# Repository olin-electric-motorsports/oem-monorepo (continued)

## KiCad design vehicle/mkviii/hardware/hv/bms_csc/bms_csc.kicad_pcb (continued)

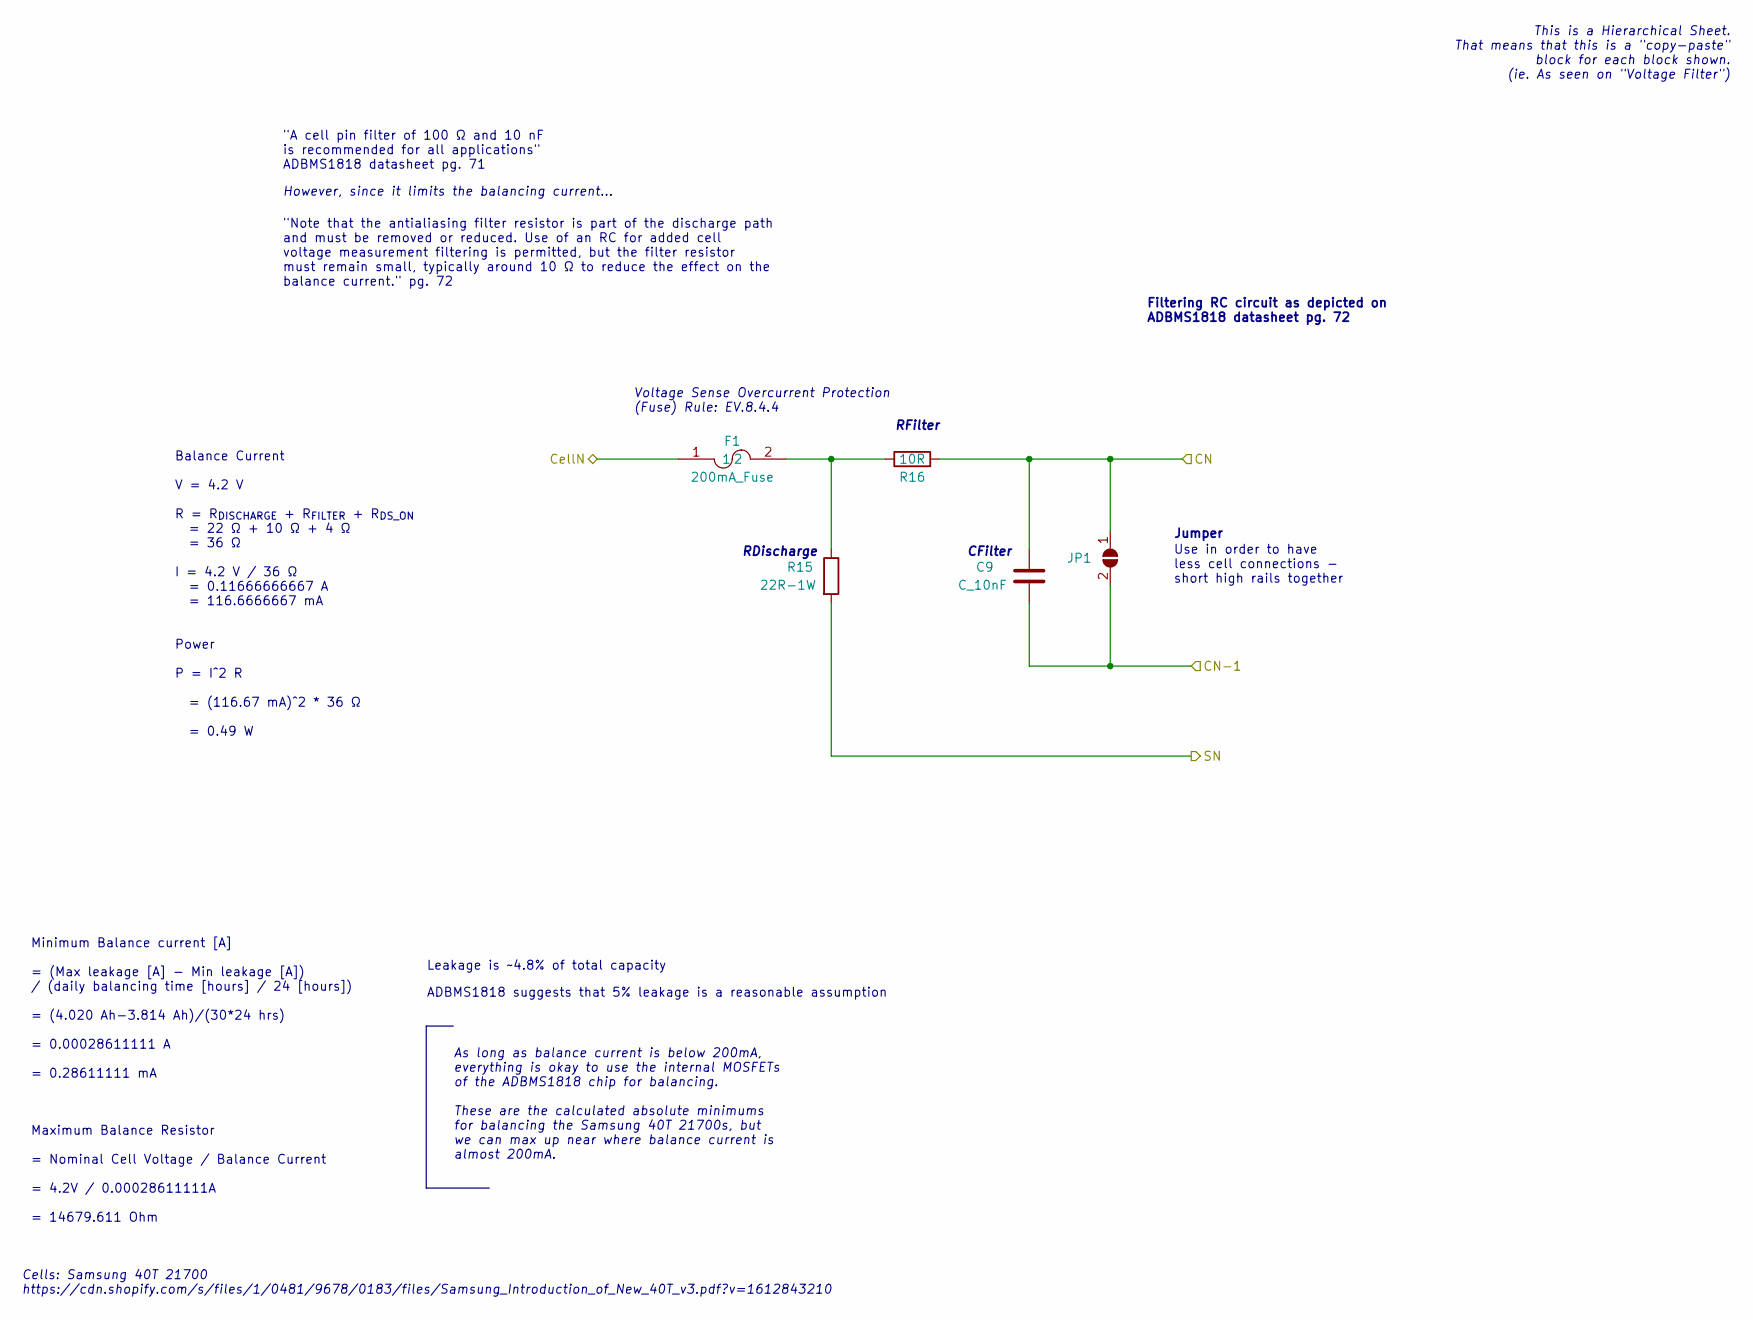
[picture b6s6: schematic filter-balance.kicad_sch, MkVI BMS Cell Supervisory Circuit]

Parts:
C9: C_10nF; C_0603; MPN CL10B103KB8NNNC
F1: 200mA_Fuse; Fuse_1206_3216Metric; MPN 0466.200NRHF
JP1: SolderJumper_2_Open; SolderJumper-2_P1.3mm_Open_TrianglePad1.0x1.5mm
R15: 22R-1W; R_2512_6332Metric; MPN 352022RJT
R16: 10R; R_0603; MPN SG73P1JTTD100J

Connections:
/C15: C9.2, JP1.2 (B); also elsewhere on the board
/C16: C9.1, JP1.1 (A), R16.2; also elsewhere on the board
/CELL16: F1.1; also elsewhere on the board
/S16: R15.2; also elsewhere on the board
unnamed: F1.2, R15.1, R16.1

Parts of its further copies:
C10, C11, C12, C13, C14, C15, C16, C17, C18, C19, C20, C21, C22, C23, C24, C25, C26: C_10nF; C_0603; MPN CL10B103KB8NNNC
F2, F3, F4, F5, F6, F7, F8, F9, F10, F11, F12, F13, F14, F15, F16, F17, F18: 200mA_Fuse; Fuse_1206_3216Metric; MPN 0466.200NRHF
JP2, JP3, JP4, JP5, JP6, JP7, JP8, JP9, JP10, JP11, JP12, JP13, JP14, JP15, JP16, JP17, JP18: SolderJumper_2_Open; SolderJumper-2_P1.3mm_Open_TrianglePad1.0x1.5mm
R17, R19, R21, R23, R25, R27, R29, R31, R33, R35, R37, R39, R41, R43, R45, R47, R49: 22R-1W; R_2512_6332Metric; MPN 352022RJT
R18, R20, R22, R24, R26, R28, R30, R32, R34, R36, R38, R40, R42, R44, R46, R48, R50: 10R; R_0603; MPN SG73P1JTTD100J

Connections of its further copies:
/C1: C25.2, C26.1, JP17.2 (B), JP18.1 (A), R50.2; also elsewhere on the board
/C2: C24.2, C25.1, JP16.2 (B), JP17.1 (A), R48.2; also elsewhere on the board
/C3: C23.2, C24.1, JP15.2 (B), JP16.1 (A), R46.2; also elsewhere on the board
/C4: C22.2, C23.1, JP14.2 (B), JP15.1 (A), R44.2; also elsewhere on the board
/C5: C21.2, C22.1, JP13.2 (B), JP14.1 (A), R42.2; also elsewhere on the board
/C6: C20.2, C21.1, JP12.2 (B), JP13.1 (A), R40.2; also elsewhere on the board
/C7: C19.2, C20.1, JP11.2 (B), JP12.1 (A), R38.2; also elsewhere on the board
/C8: C18.2, C19.1, JP10.2 (B), JP11.1 (A), R36.2; also elsewhere on the board
/C9: C17.2, C18.1, JP9.2 (B), JP10.1 (A), R34.2; also elsewhere on the board
/C10: C16.2, C17.1, JP8.2 (B), JP9.1 (A), R32.2; also elsewhere on the board
/C11: C15.2, C16.1, JP7.2 (B), JP8.1 (A), R30.2; also elsewhere on the board
/C12: C14.2, C15.1, JP6.2 (B), JP7.1 (A), R28.2; also elsewhere on the board
/C13: C13.2, C14.1, JP5.2 (B), JP6.1 (A), R26.2; also elsewhere on the board
/C14: C12.2, C13.1, JP4.2 (B), JP5.1 (A), R24.2; also elsewhere on the board
/C15: C12.1, JP4.1 (A), R22.2; also elsewhere on the board
/C16: C11.2, JP3.2 (B); also elsewhere on the board
/C17: C10.2, C11.1, JP2.2 (B), JP3.1 (A), R20.2; also elsewhere on the board
/C18: C10.1, JP2.1 (A), R18.2; also elsewhere on the board
/CELL1: F18.1; also elsewhere on the board
/CELL2: F17.1; also elsewhere on the board
/CELL3: F16.1; also elsewhere on the board
/CELL4: F15.1; also elsewhere on the board
/CELL5: F14.1; also elsewhere on the board
/CELL6: F13.1; also elsewhere on the board
/CELL7: F12.1; also elsewhere on the board
/CELL8: F11.1; also elsewhere on the board
/CELL9: F10.1; also elsewhere on the board
/CELL10: F9.1; also elsewhere on the board
/CELL11: F8.1; also elsewhere on the board
/CELL12: F7.1; also elsewhere on the board
/CELL13: F6.1; also elsewhere on the board
/CELL14: F5.1; also elsewhere on the board
/CELL15: F4.1; also elsewhere on the board
/CELL17: F3.1; also elsewhere on the board
/CELL18: F2.1; also elsewhere on the board
/S1: R49.2; also elsewhere on the board
/S2: R47.2; also elsewhere on the board
/S3: R45.2; also elsewhere on the board
/S4: R43.2; also elsewhere on the board
/S5: R41.2; also elsewhere on the board
/S6: R39.2; also elsewhere on the board
/S7: R37.2; also elsewhere on the board
/S8: R35.2; also elsewhere on the board
/S9: R33.2; also elsewhere on the board
/S10: R31.2; also elsewhere on the board
/S11: R29.2; also elsewhere on the board
/S12: R27.2; also elsewhere on the board
/S13: R25.2; also elsewhere on the board
/S14: R23.2; also elsewhere on the board
/S15: R21.2; also elsewhere on the board
/S17: R19.2; also elsewhere on the board
/S18: R17.2; also elsewhere on the board
unnamed: F2.2, R17.1, R18.1
unnamed: F3.2, R19.1, R20.1
unnamed: F4.2, R21.1, R22.1
unnamed: F5.2, R23.1, R24.1
unnamed: F6.2, R25.1, R26.1
unnamed: F7.2, R27.1, R28.1
unnamed: F8.2, R29.1, R30.1
unnamed: F9.2, R31.1, R32.1
unnamed: F10.2, R33.1, R34.1
unnamed: F11.2, R35.1, R36.1
unnamed: F12.2, R37.1, R38.1
unnamed: F13.2, R39.1, R40.1
unnamed: F14.2, R41.1, R42.1
unnamed: F15.2, R43.1, R44.1
unnamed: F16.2, R45.1, R46.1
unnamed: F17.2, R47.1, R48.1
unnamed: F18.2, R49.1, R50.1

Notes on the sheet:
RDischarge
Leakage is ~4.8% of total capacity
Use in order to have less cell connections - short high rails together
"A cell pin filter of 100 Ω and 10 nF is recommended for all applications" ADBMS1818 datasheet pg. 71
This is a Hierarchical Sheet. That means that this is a "copy-paste" block for each block shown. (ie. As seen on "Voltage Filter")
CFilter
"Note that the antialiasing filter resistor is part of the discharge path and must be removed or reduced. Use of an RC for added cell voltage measurement filtering is permitted, but the filter resistor must remain small, typically around 10 Ω to reduce the effect on the balance current." pg. 72
Maximum Balance Resistor = Nominal Cell Voltage / Balance Current = 4.2V / 0.00028611111A = 14679.611 Ohm
However, since it limits the balancing current...
Minimum Balance current [A] = (Max leakage [A] - Min leakage [A]) / (daily balancing time [hours] / 24 [hours]) = (4.020 Ah-3.814 Ah)/(30*24 hrs) = 0.00028611111 A = 0.28611111 mA
ADBMS1818 suggests that 5% leakage is a reasonable assumption
Jumper
Voltage Sense Overcurrent Protection (Fuse) Rule: EV.8.4.4
As long as balance current is below 200mA, everything is okay to use the internal MOSFETs of the ADBMS1818 chip for balancing. These are the calculated absolute minimums for balancing the Samsung 40T 21700s, but we can max up near where balance current is almost 200mA.
Filtering RC circuit as depicted on ADBMS1818 datasheet pg. 72
RFilter
Balance Current V = 4.2 V R = R_{DISCHARGE} + R_{FILTER} + R_{DS_ON} = 22 Ω + 10 Ω + 4 Ω = 36 Ω I = 4.2 V / 36 Ω = 0.11666666667 A = 116.6666667 mA Power P = I^2 R = (116.67 mA)^2 * 36 Ω = 0.49 W
Cells: Samsung 40T 21700 https://cdn.shopify.com/s/files/1/0481/9678/0183/files/Samsung_Introduction_of_New_40T_v3.pdf?v=1612843210

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
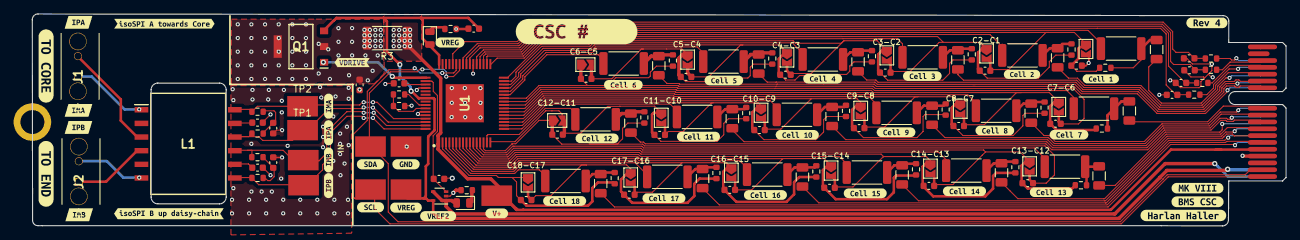
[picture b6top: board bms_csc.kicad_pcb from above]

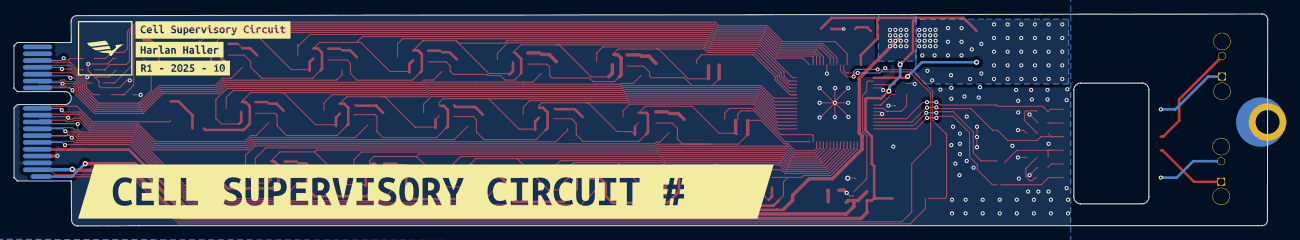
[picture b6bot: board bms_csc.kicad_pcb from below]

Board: 2 copper layers, 183.7 x 31.1 mm, 181 parts (4 on the bottom side), 106 nets.

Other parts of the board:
kibuzzard-63B4D82F: G***; kibuzzard-63B4D82F
kibuzzard-63B4D834: G***; kibuzzard-63B4D834
kibuzzard-63B4E58E: G***; kibuzzard-63B4E58E
kibuzzard-63B4E59A: G***; kibuzzard-63B4E59A
kibuzzard-63B4E581: G***; kibuzzard-63B4E581
kibuzzard-63B4E593: G***; kibuzzard-63B4E593
kibuzzard-63B4EB9B: G***; kibuzzard-63B4EB9B
kibuzzard-63B4EBA9: G***; kibuzzard-63B4EBA9
kibuzzard-63B4EBAD: G***; kibuzzard-63B4EBAD
kibuzzard-63B4EBB3: G***; kibuzzard-63B4EBB3
kibuzzard-63B4EBB8: G***; kibuzzard-63B4EBB8
kibuzzard-63B4EBF9: G***; kibuzzard-63B4EBF9
kibuzzard-63B4EC1B: G***; kibuzzard-63B4EC1B
kibuzzard-63B4EC4E: G***; kibuzzard-63B4EC4E
kibuzzard-63B4EC5B: G***; kibuzzard-63B4EC5B
kibuzzard-63B4EC6B: G***; kibuzzard-63B4EC6B
kibuzzard-63B4EC7A: G***; kibuzzard-63B4EC7A
kibuzzard-63B4EC20: G***; kibuzzard-63B4EC20
kibuzzard-63B4EC53: G***; kibuzzard-63B4EC53
kibuzzard-63B4EC66: G***; kibuzzard-63B4EC66
kibuzzard-63B4EC74: G***; kibuzzard-63B4EC74
kibuzzard-63B4EC80: G***; kibuzzard-63B4EC80
kibuzzard-63B4ED2A: G***; kibuzzard-63B4ED2A
kibuzzard-63B4ED25: G***; kibuzzard-63B4ED25
kibuzzard-63B4ED94: G***; kibuzzard-63B4ED94
kibuzzard-673A717E: G***; kibuzzard-673A717E
kibuzzard-673A718C: G***; kibuzzard-673A718C
kibuzzard-673A725C: G***; kibuzzard-673A725C
kibuzzard-673A7176: G***; kibuzzard-673A7176
kibuzzard-673A7184: G***; kibuzzard-673A7184
kibuzzard-673AA1F5: G***; kibuzzard-673AA1F5
kibuzzard-673AA1FB: G***; kibuzzard-673AA1FB
kibuzzard-673AA20C: G***; kibuzzard-673AA20C
kibuzzard-673AA233: G***; kibuzzard-673AA233
kibuzzard-691FAACE: G***; kibuzzard-691FAACE
kibuzzard-6736A7FC: G***; kibuzzard-6736A7FC
kibuzzard-6736A805: G***; kibuzzard-6736A805
kibuzzard-6736A828: G***; kibuzzard-6736A828
kibuzzard-6736A857: G***; kibuzzard-6736A857
kibuzzard-6736A863: G***; kibuzzard-6736A863
kibuzzard-6902CBBF: G***; kibuzzard-6902CBBF
kibuzzard-6902E3D6: G***; kibuzzard-6902E3D6
kibuzzard-673993C6: G***; kibuzzard-673993C6
kibuzzard-673998AC: G***; kibuzzard-673998AC
kibuzzard-69001352: G***; kibuzzard-69001352
kibuzzard-69001366: G***; kibuzzard-69001366
kibuzzard-69001374: G***; kibuzzard-69001374

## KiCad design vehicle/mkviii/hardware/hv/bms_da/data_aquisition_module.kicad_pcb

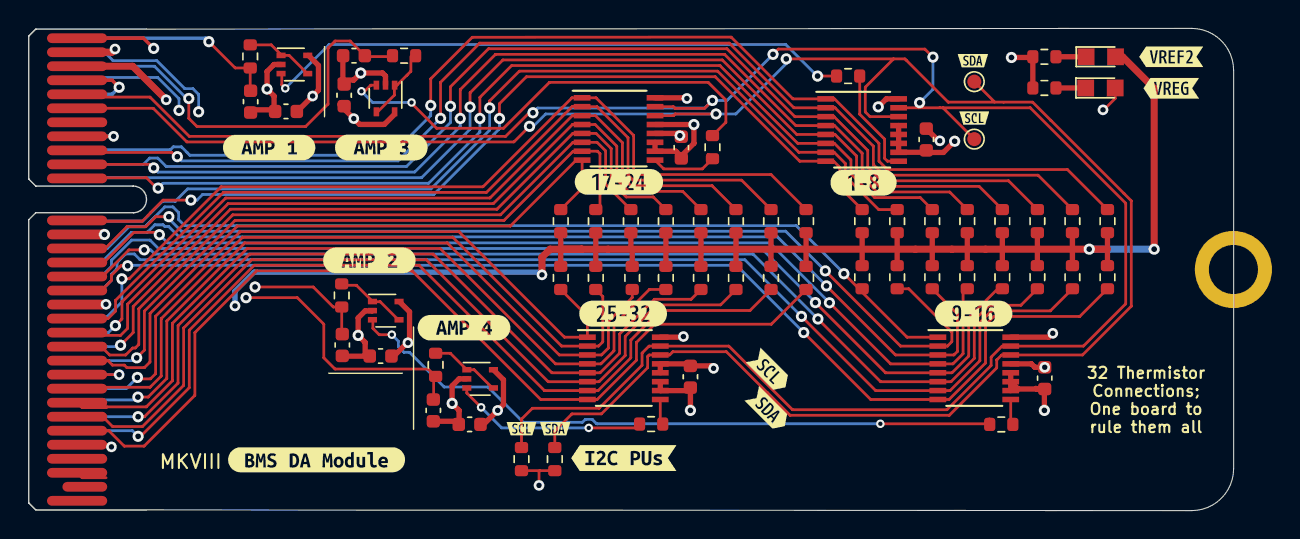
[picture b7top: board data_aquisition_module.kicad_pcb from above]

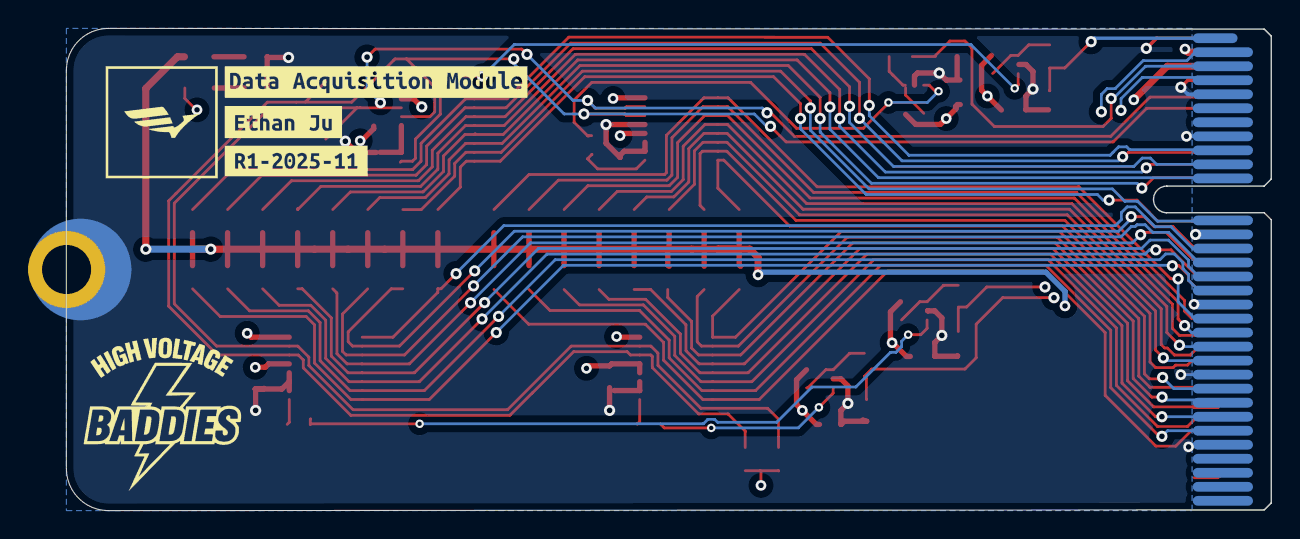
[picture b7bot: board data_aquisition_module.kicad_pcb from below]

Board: 4 copper layers, 86.0 x 34.4 mm, 91 parts (3 on the bottom side), 55 nets.

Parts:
C1, C2, C3, C4: C_1uF; C_0603
C5, C6, C7, C8, C9, C10, C11, C12: 1uF; C_0603
H2: CONN_MountingHole; PCIe_Mount
J1: CONN_pcie_x4; pcie_x4
PD1, PD2: WHITE; CHIPLED_0805
R1, R2, R3, R4, R5, R6, R7, R8, R9, R10, R11, R12, R13, R14, R15, R16, R17, R18, R19, R20, R21, R22, R23, R24, R25, R26, R27, R28, R29, R30, R31, R32: R_100K; R_0603
R33, R35, R37, R39: 1M; R_0603
R34, R36, R38, R40: 3.3K; R_0603
R41, R42: 1KR; R_0603
R43, R44: 4.7K; R_0603
TP1, TP2: TP_1mm; TestPoint_Pad_D1.0mm
U1, U2, U3, U4: LTC1380IGN; SSOP-16_3.9x4.9mm_P0.635mm
U5, U6, U7, U8: MCP6001T-I-LT; SOT-353_SC-70-5
kibuzzard-63A54BB0: G***; kibuzzard-63A54BB0
kibuzzard-63A54BCB: G***; kibuzzard-63A54BCB
kibuzzard-63A54BE3: G***; kibuzzard-63A54BE3
kibuzzard-63BF51CA: G***; kibuzzard-63BF51CA
kibuzzard-63BF55B8: G***; kibuzzard-63BF55B8
kibuzzard-63BF55D1: G***; kibuzzard-63BF55D1
kibuzzard-672C3C6B, kibuzzard-672C3C6B#2: G***; kibuzzard-672C3C6B
kibuzzard-672C3C52, kibuzzard-672C3C52#2: G***; kibuzzard-672C3C52
kibuzzard-672C38BF: G***; kibuzzard-672C38BF
kibuzzard-673B8AB7: G***; kibuzzard-673B8AB7
kibuzzard-673B8ABD: G***; kibuzzard-673B8ABD
kibuzzard-673B8BCC: G***; kibuzzard-673B8BCC
kibuzzard-673B8DE4: G***; kibuzzard-673B8DE4
kibuzzard-673B8DEE: G***; kibuzzard-673B8DEE
kibuzzard-6920C4AE: G***; kibuzzard-6920C4AE
kibuzzard-6920C49E: G***; kibuzzard-6920C49E
kibuzzard-66171EA1: G***; kibuzzard-66171EA1
kibuzzard-66171EC5: G***; kibuzzard-66171EC5
kibuzzard-661723CB: G***; kibuzzard-661723CB

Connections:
/MUX_1_OUT: C12.1, J1.A1 (Aout_0), R34.1
/MUX_2_OUT: C10.1, J1.A2 (Aout_1), R36.1
/MUX_3_OUT: C8.1, J1.A3 (Aout_2), R38.1
/MUX_4_OUT: C6.1, J1.A4 (Aout_3), R40.1
/SCL: J1.B5 (SCL), R43.1, TP1.1, U1.15 (SCL), U2.15 (SCL), U3.15 (SCL), U4.15 (SCL)
/SDA: J1.B6 (SDA), R44.1, TP2.1, U1.14 (SDA), U2.14 (SDA), U3.14 (SDA), U4.14 (SDA)
/THERM_1: J1.A9 (Ain_0), R1.2, U1.1 (S0)
/THERM_2: J1.B9 (Ain_1), R2.2, U1.2 (S1)
/THERM_3: J1.A10 (Ain_2), R3.2, U1.3 (S2)
/THERM_4: J1.B10 (Ain_3), R4.2, U1.4 (S3)
/THERM_5: J1.A11 (Ain_4), R5.2, U1.5 (S4)
/THERM_6: J1.B11 (Ain_5), R6.2, U1.6 (S5)
/THERM_7: J1.A12 (Ain_6), R7.2, U1.7 (S6)
/THERM_8: J1.B12 (Ain_7), R8.2, U1.8 (S7)
/THERM_9: J1.A14 (Ain_8), R9.2, U2.1 (S0)
/THERM_10: J1.B14 (Ain_9), R10.2, U2.2 (S1)
/THERM_11: J1.A15 (Ain_10), R11.2, U2.3 (S2)
/THERM_12: J1.B15 (Ain_11), R12.2, U2.4 (S3)
/THERM_13: J1.A16 (Ain_12), R13.2, U2.5 (S4)
/THERM_14: J1.B16 (Ain_13), R14.2, U2.6 (S5)
/THERM_15: J1.A17 (Ain_14), R15.2, U2.7 (S6)
/THERM_16: J1.B17 (Ain_15), R16.2, U2.8 (S7)
/THERM_17: J1.A19 (Ain_16), R17.2, U3.1 (S0)
/THERM_18: J1.B19 (Ain_17), R18.2, U3.2 (S1)
/THERM_19: J1.A20 (Ain_18), R19.2, U3.3 (S2)
/THERM_20: J1.B20 (Ain_19), R20.2, U3.4 (S3)
/THERM_21: J1.A21 (Ain_20), R21.2, U3.5 (S4)
/THERM_22: J1.B21 (Ain_21), R22.2, U3.6 (S5)
/THERM_23: J1.A22 (Ain_22), R23.2, U3.7 (S6)
/THERM_24: J1.B22 (Ain_23), R24.2, U3.8 (S7)
/THERM_25: J1.A24 (Ain_24), R25.2, U4.1 (S0)
/THERM_26: J1.B24 (Ain_25), R26.2, U4.2 (S1)
/THERM_27: J1.A25 (Ain_26), R27.2, U4.3 (S2)
/THERM_28: J1.B25 (Ain_27), R28.2, U4.4 (S3)
/THERM_29: J1.A26 (Ain_28), R29.2, U4.5 (S4)
/THERM_30: J1.B26 (Ain_29), R30.2, U4.6 (S5)
/THERM_31: J1.A27 (Ain_30), R31.2, U4.7 (S6)
/THERM_32: J1.B27 (Ain_31), R32.2, U4.8 (S7)
/VREF2: J1.B3 (3V), PD2.2 (A), R1.1, R2.1, R3.1, R4.1, R5.1, R6.1, R7.1, R8.1, R9.1, R10.1, R11.1, R12.1, R13.1, R14.1, R15.1, R16.1, R17.1, R18.1, R19.1, R20.1, R21.1, R22.1, R23.1, R24.1, R25.1, R26.1, R27.1, R28.1, R29.1, R30.1, R31.1, R32.1
/VREG: C1.1, C2.1, C3.1, C4.1, C5.1, C7.1, C9.1, C11.1, J1.B2 (5V), PD1.2 (A), R43.2, R44.2, U1.16 (VCC), U2.13 (A0), U2.16 (VCC), U3.12 (A1), U3.16 (VCC), U4.12 (A1), U4.13 (A0), U4.16 (VCC), U5.5 (V+), U6.5 (V+), U7.5 (V+), U8.5 (V+)
GND: C1.2, C2.2, C3.2, C4.2, C5.2, C6.2, C7.2, C8.2, C9.2, C10.2, C11.2, C12.2, H2.1, J1.A5 (GND), J1.A8 (GND), J1.A13 (GND), J1.A18 (GND), J1.A23 (GND), J1.A28 (GND), J1.B1 (GND), J1.B4 (GND), J1.B8 (GND), J1.B13 (GND), J1.B18 (GND), J1.B23 (GND), J1.B28 (GND), R41.2, R42.2, U1.10 (VEE), U1.11 (GND), U1.12 (A1), U1.13 (A0), U2.10 (VEE), U2.11 (GND), U2.12 (A1), U3.10 (VEE), U3.11 (GND), U3.13 (A0), U4.10 (VEE), U4.11 (GND), U5.2 (V-), U6.2 (V-), U7.2 (V-), U8.2 (V-)
unnamed: PD1.1 (K), R41.1
unnamed: PD2.1 (K), R42.1
unnamed: R33.1, U1.9 (D0)
unnamed: R35.1, U2.9 (D0)
unnamed: R37.1, U3.9 (D0)
unnamed: R39.1, U4.9 (D0)
unnamed: R39.2, U5.3 (+)
unnamed: R40.2, U5.1, U5.4 (-)
unnamed: R37.2, U6.3 (+)
unnamed: R38.2, U6.1, U6.4 (-)
unnamed: R35.2, U7.3 (+)
unnamed: R36.2, U7.1, U7.4 (-)
unnamed: R33.2, U8.3 (+)
unnamed: R34.2, U8.1, U8.4 (-)
